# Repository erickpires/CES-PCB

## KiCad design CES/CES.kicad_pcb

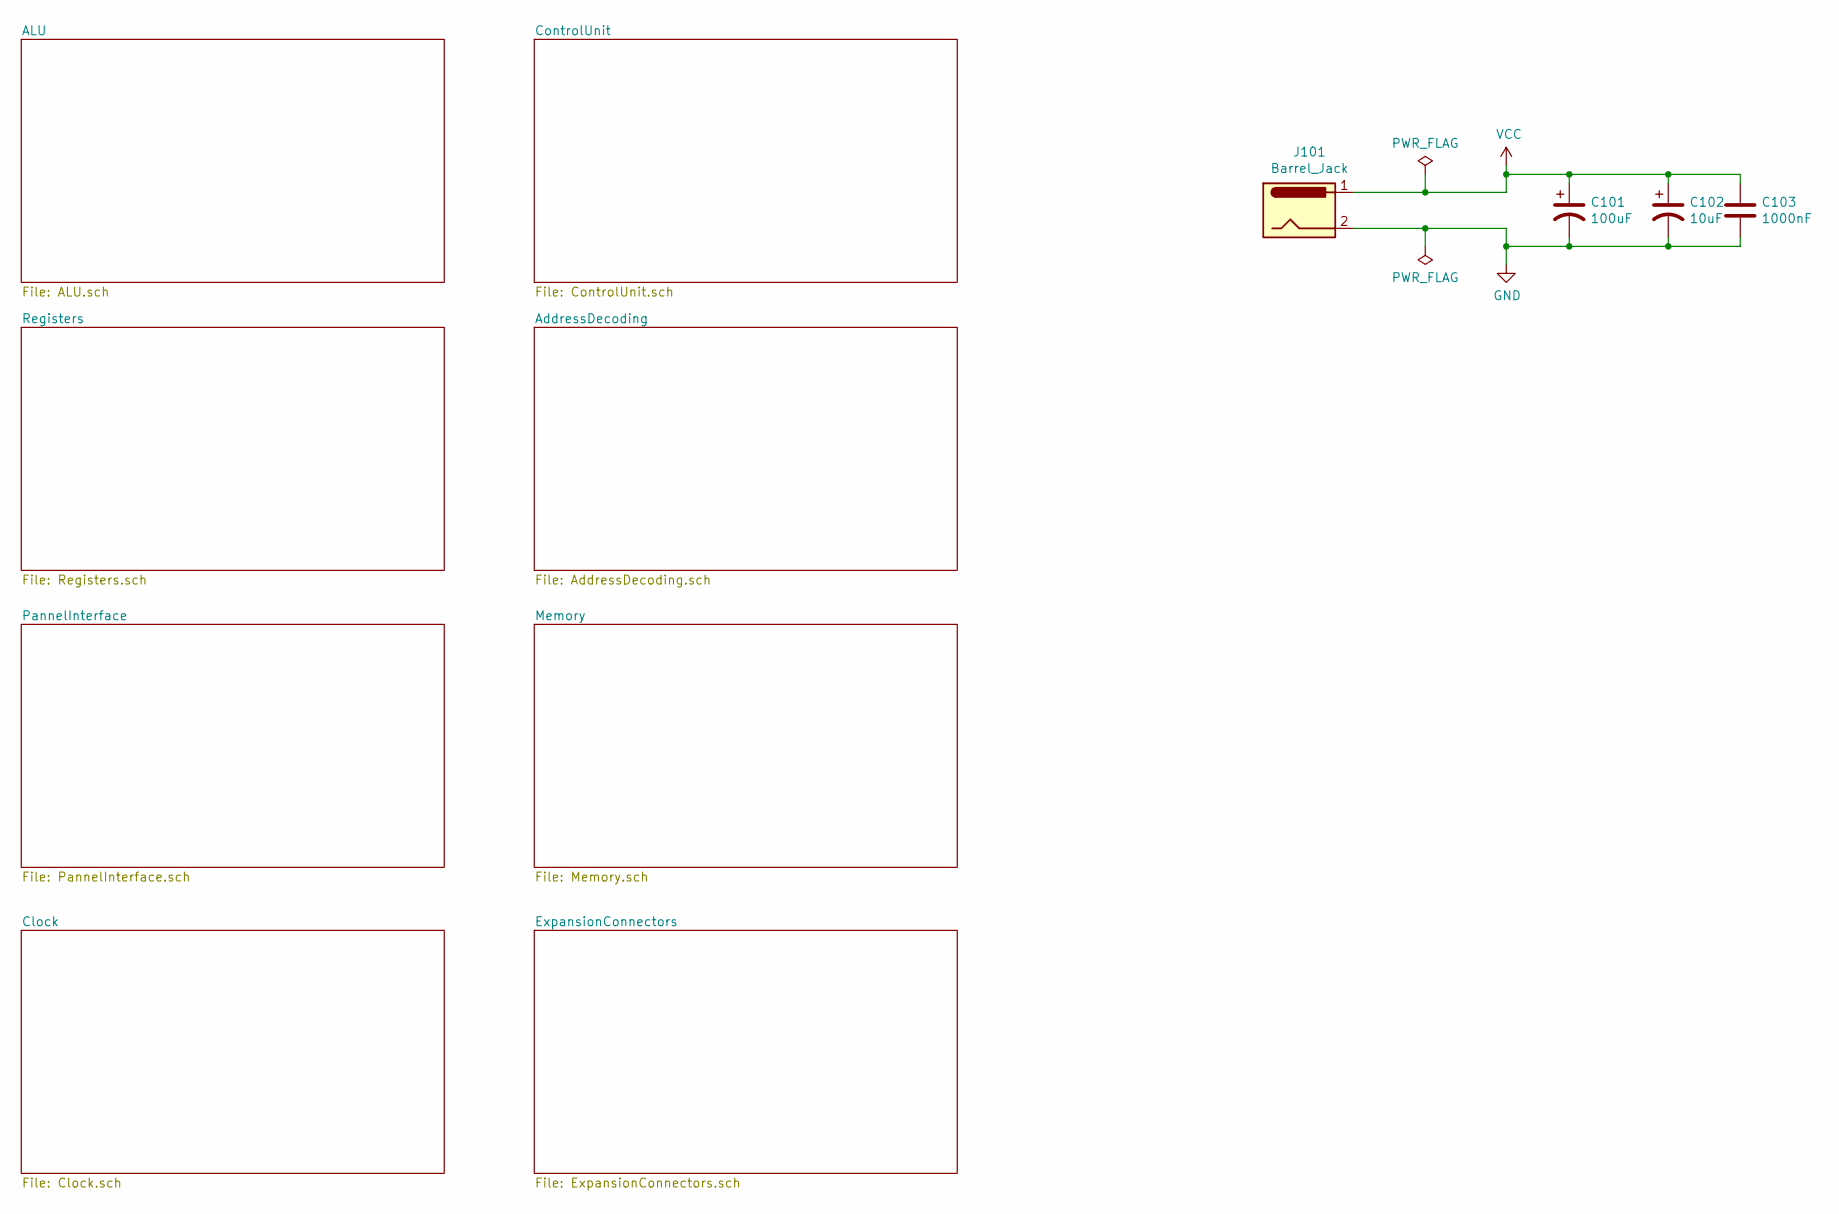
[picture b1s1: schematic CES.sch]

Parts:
C101: 100uF
C102: 10uF
C103: 1000nF
J101: Barrel_Jack

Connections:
GND: C101.2, C102.2, C103.2, J101.2; also elsewhere on the board
VCC: C101.1, C102.1, C103.1, J101.1; also elsewhere on the board

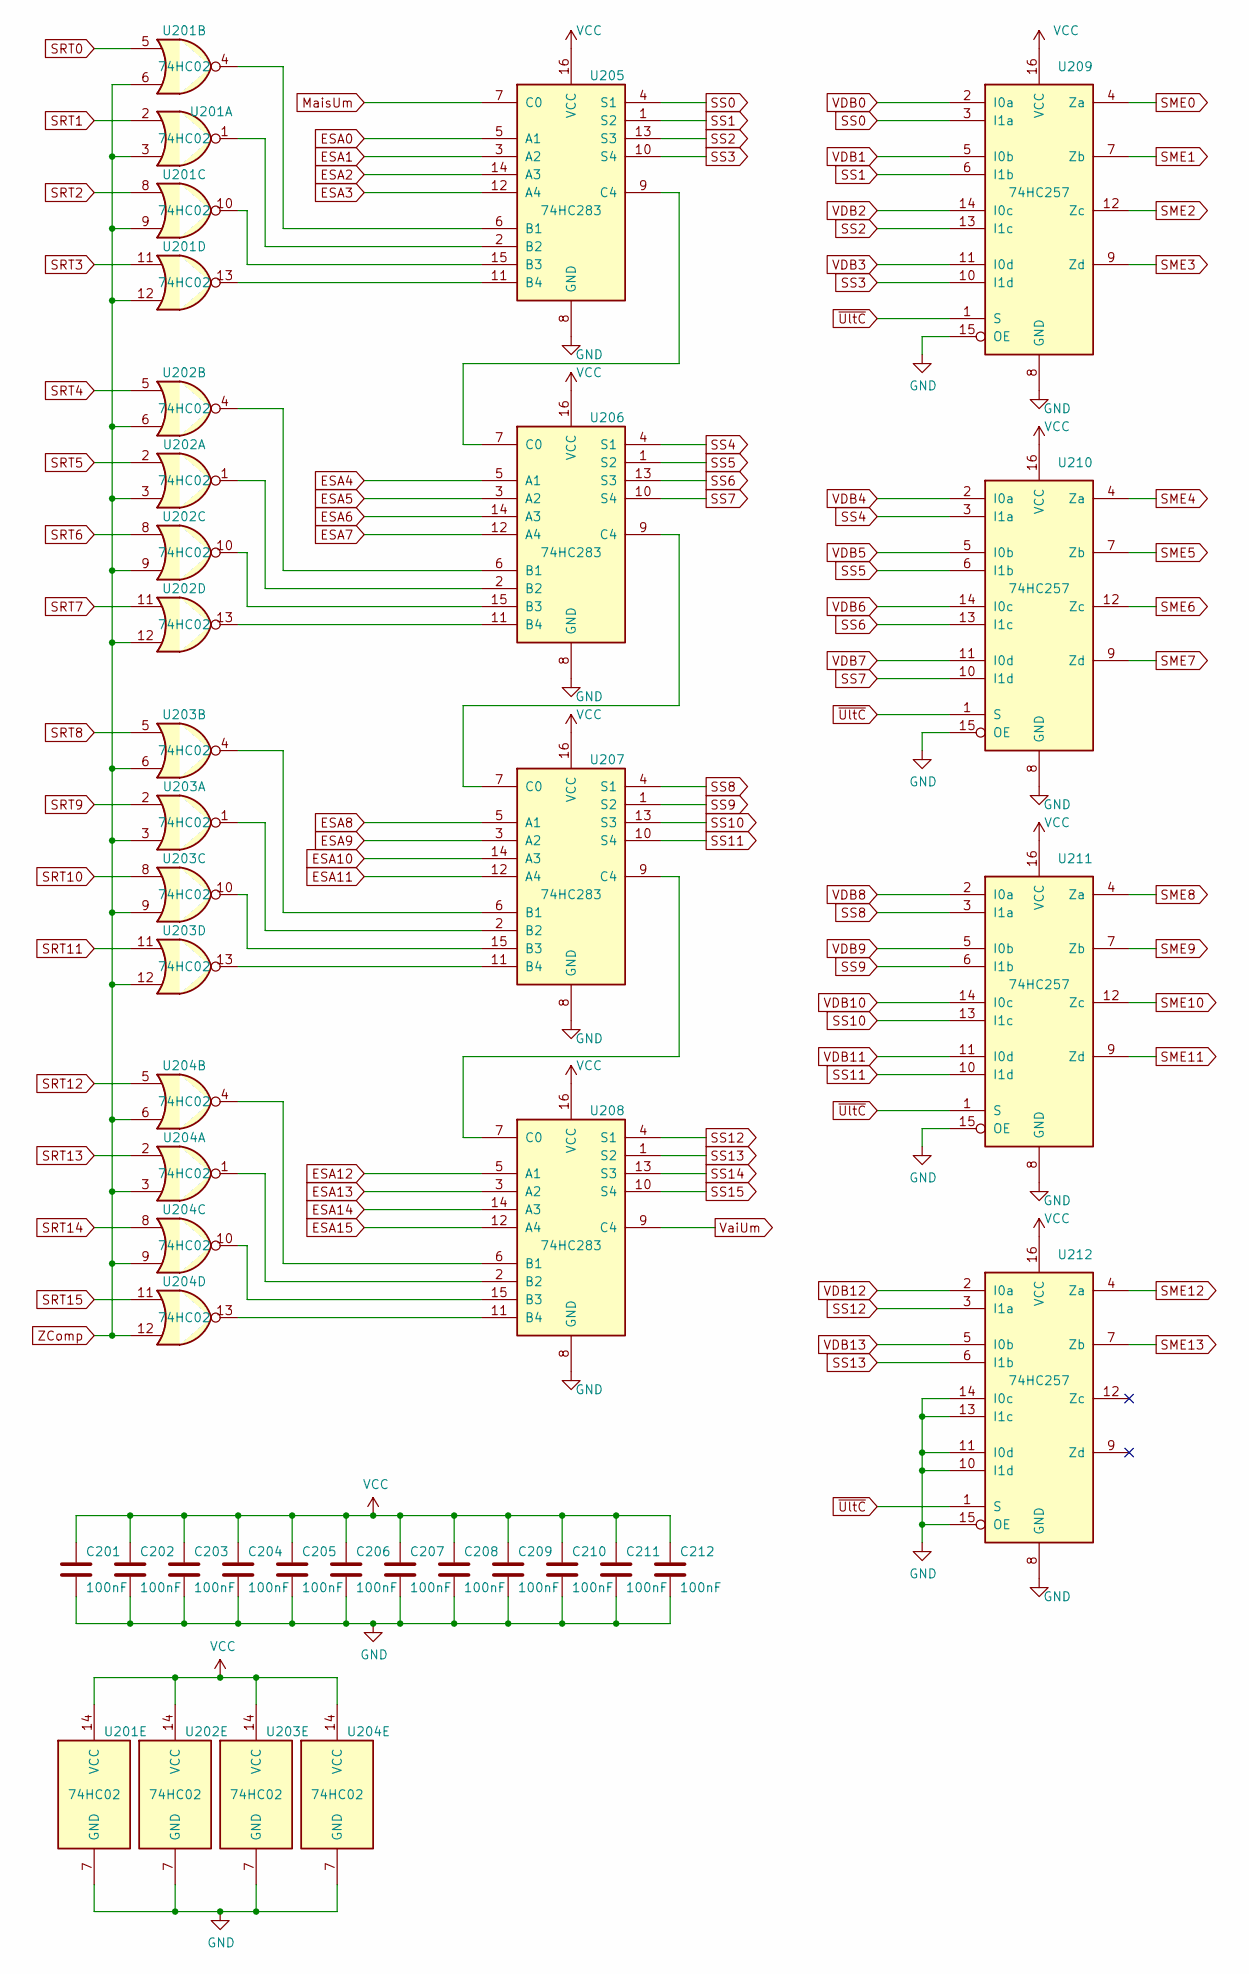
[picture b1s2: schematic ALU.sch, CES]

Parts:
C201, C202, C203, C204, C205, C206, C207, C208, C209, C210, C211, C212: 100nF; C_Disc_D4.3mm_W1.9mm_P5.00mm
U201, U202, U203, U204: 74HC02; DIP-14_W7.62mm
U205, U206, U207, U208: 74HC283; DIP-16_W7.62mm
U209, U210, U211, U212: 74HC257; DIP-16_W7.62mm

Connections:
ESA0: U205.5 (A1); also elsewhere on the board
ESA1: U205.3 (A2); also elsewhere on the board
ESA2: U205.14 (A3); also elsewhere on the board
ESA3: U205.12 (A4); also elsewhere on the board
ESA4: U206.5 (A1); also elsewhere on the board
ESA5: U206.3 (A2); also elsewhere on the board
ESA6: U206.14 (A3); also elsewhere on the board
ESA7: U206.12 (A4); also elsewhere on the board
ESA8: U207.5 (A1); also elsewhere on the board
ESA9: U207.3 (A2); also elsewhere on the board
ESA10: U207.14 (A3); also elsewhere on the board
ESA11: U207.12 (A4); also elsewhere on the board
ESA12: U208.5 (A1); also elsewhere on the board
ESA13: U208.3 (A2); also elsewhere on the board
ESA14: U208.14 (A3); also elsewhere on the board
ESA15: U208.12 (A4); also elsewhere on the board
GND: C201.2, C202.2, C203.2, C204.2, C205.2, C206.2, C207.2, C208.2, C209.2, C210.2, C211.2, C212.2, U201.7 (GND), U202.7 (GND), U203.7 (GND), U204.7 (GND), U205.8 (GND), U206.8 (GND), U207.8 (GND), U208.8 (GND), U209.8 (GND), U209.15 (OE), U210.8 (GND), U210.15 (OE), U211.8 (GND), U211.15 (OE), U212.8 (GND), U212.10 (I1d), U212.11 (I0d), U212.13 (I1c), U212.14 (I0c), U212.15 (OE); also elsewhere on the board
MaisUm: U205.7 (C0); also elsewhere on the board
unnamed: U201.1, U205.2 (B2)
unnamed: U201.4, U205.6 (B1)
unnamed: U201.10, U205.15 (B3)
unnamed: U201.13, U205.11 (B4)
unnamed: U202.1, U206.2 (B2)
unnamed: U202.4, U206.6 (B1)
unnamed: U202.10, U206.15 (B3)
unnamed: U202.13, U206.11 (B4)
unnamed: U203.1, U207.2 (B2)
unnamed: U203.4, U207.6 (B1)
unnamed: U203.10, U207.15 (B3)
unnamed: U203.13, U207.11 (B4)
unnamed: U204.1, U208.2 (B2)
unnamed: U204.4, U208.6 (B1)
unnamed: U204.10, U208.15 (B3)
unnamed: U204.13, U208.11 (B4)
unnamed: U205.9 (C4), U206.7 (C0)
unnamed: U206.9 (C4), U207.7 (C0)
unnamed: U207.9 (C4), U208.7 (C0)
SME0: U209.4 (Za); also elsewhere on the board
SME1: U209.7 (Zb); also elsewhere on the board
SME2: U209.12 (Zc); also elsewhere on the board
SME3: U209.9 (Zd); also elsewhere on the board
SME4: U210.4 (Za); also elsewhere on the board
SME5: U210.7 (Zb); also elsewhere on the board
SME6: U210.12 (Zc); also elsewhere on the board
SME7: U210.9 (Zd); also elsewhere on the board
SME8: U211.4 (Za); also elsewhere on the board
SME9: U211.7 (Zb); also elsewhere on the board
SME10: U211.12 (Zc); also elsewhere on the board
SME11: U211.9 (Zd); also elsewhere on the board
SME12: U212.4 (Za); also elsewhere on the board
SME13: U212.7 (Zb); also elsewhere on the board
SRT0: U201.5; also elsewhere on the board
SRT1: U201.2; also elsewhere on the board
SRT2: U201.8; also elsewhere on the board
SRT3: U201.11; also elsewhere on the board
SRT4: U202.5; also elsewhere on the board
SRT5: U202.2; also elsewhere on the board
SRT6: U202.8; also elsewhere on the board
SRT7: U202.11; also elsewhere on the board
SRT8: U203.5; also elsewhere on the board
SRT9: U203.2; also elsewhere on the board
SRT10: U203.8; also elsewhere on the board
SRT11: U203.11; also elsewhere on the board
SRT12: U204.5; also elsewhere on the board
SRT13: U204.2; also elsewhere on the board
SRT14: U204.8; also elsewhere on the board
SRT15: U204.11; also elsewhere on the board
SS0: U205.4 (S1), U209.3 (I1a); also elsewhere on the board
SS1: U205.1 (S2), U209.6 (I1b); also elsewhere on the board
SS2: U205.13 (S3), U209.13 (I1c); also elsewhere on the board
SS3: U205.10 (S4), U209.10 (I1d); also elsewhere on the board
SS4: U206.4 (S1), U210.3 (I1a); also elsewhere on the board
SS5: U206.1 (S2), U210.6 (I1b); also elsewhere on the board
SS6: U206.13 (S3), U210.13 (I1c); also elsewhere on the board
SS7: U206.10 (S4), U210.10 (I1d); also elsewhere on the board
SS8: U207.4 (S1), U211.3 (I1a); also elsewhere on the board
SS9: U207.1 (S2), U211.6 (I1b); also elsewhere on the board
SS10: U207.13 (S3), U211.13 (I1c); also elsewhere on the board
SS11: U207.10 (S4), U211.10 (I1d); also elsewhere on the board
SS12: U208.4 (S1), U212.3 (I1a); also elsewhere on the board
SS13: U208.1 (S2), U212.6 (I1b); also elsewhere on the board
SS14: U208.13 (S3); also elsewhere on the board
SS15: U208.10 (S4); also elsewhere on the board
VCC: C201.1, C202.1, C203.1, C204.1, C205.1, C206.1, C207.1, C208.1, C209.1, C210.1, C211.1, C212.1, U201.14 (VCC), U202.14 (VCC), U203.14 (VCC), U204.14 (VCC), U205.16 (VCC), U206.16 (VCC), U207.16 (VCC), U208.16 (VCC), U209.16 (VCC), U210.16 (VCC), U211.16 (VCC), U212.16 (VCC); also elsewhere on the board
VDB0: U209.2 (I0a); also elsewhere on the board
VDB1: U209.5 (I0b); also elsewhere on the board
VDB2: U209.14 (I0c); also elsewhere on the board
VDB3: U209.11 (I0d); also elsewhere on the board
VDB4: U210.2 (I0a); also elsewhere on the board
VDB5: U210.5 (I0b); also elsewhere on the board
VDB6: U210.14 (I0c); also elsewhere on the board
VDB7: U210.11 (I0d); also elsewhere on the board
VDB8: U211.2 (I0a); also elsewhere on the board
VDB9: U211.5 (I0b); also elsewhere on the board
VDB10: U211.14 (I0c); also elsewhere on the board
VDB11: U211.11 (I0d); also elsewhere on the board
VDB12: U212.2 (I0a); also elsewhere on the board
VDB13: U212.5 (I0b); also elsewhere on the board
VaiUm: U208.9 (C4); also elsewhere on the board
ZComp: U201.3, U201.6, U201.9, U201.12, U202.3, U202.6, U202.9, U202.12, U203.3, U203.6, U203.9, U203.12, U204.3, U204.6, U204.9, U204.12; also elsewhere on the board
~UltC: U209.1 (S), U210.1 (S), U211.1 (S), U212.1 (S); also elsewhere on the board

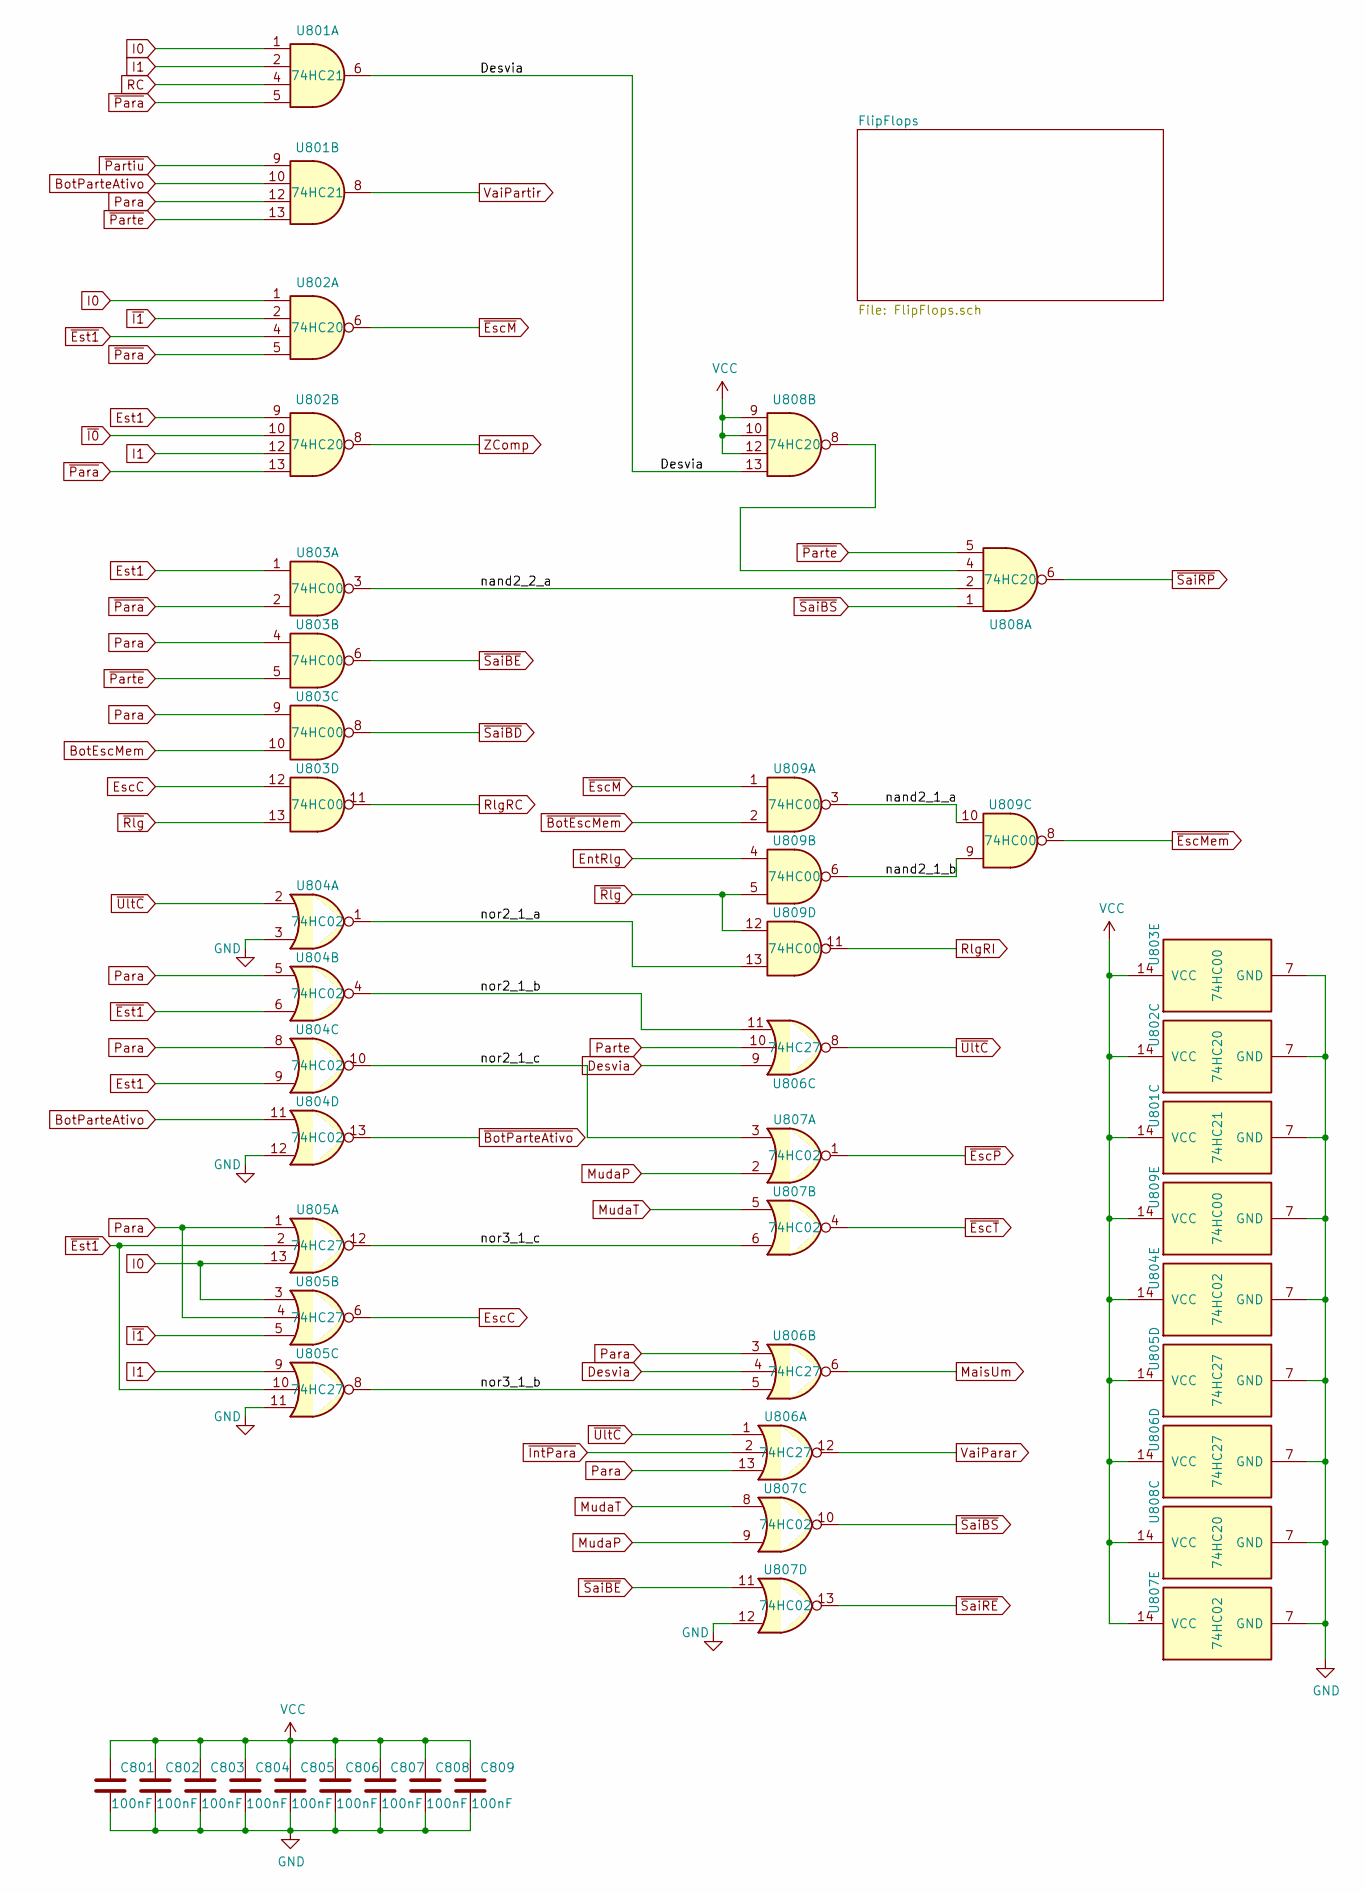
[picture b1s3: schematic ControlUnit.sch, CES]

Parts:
C801, C802, C803, C804, C805, C806, C807, C808, C809: 100nF; C_Disc_D4.3mm_W1.9mm_P5.00mm
U801: 74HC21; DIP-14_W7.62mm
U802, U808: 74HC20; DIP-14_W7.62mm
U803, U809: 74HC00; DIP-14_W7.62mm
U804, U807: 74HC02; DIP-14_W7.62mm
U805, U806: 74HC27; DIP-14_W7.62mm

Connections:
/ControlUnit/nand2_1_a: U809.3, U809.10
/ControlUnit/nand2_1_b: U809.6, U809.9
/ControlUnit/nand2_2_a: U803.3, U808.2
/ControlUnit/nor2_1_a: U804.1, U809.13
/ControlUnit/nor2_1_b: U804.4, U806.11
/ControlUnit/nor2_1_c: U804.10, U807.3
/ControlUnit/nor3_1_b: U805.8, U806.5
/ControlUnit/nor3_1_c: U805.12, U807.6
BotEscMem: U803.10; also elsewhere on the board
BotParteAtivo: U801.10, U804.11; also elsewhere on the board
Desvia: U801.6, U806.4, U806.9, U808.13
EntRlg: U809.4; also elsewhere on the board
EscC: U803.12, U805.6
Est1: U802.9, U803.1, U804.9; also elsewhere on the board
GND: C801.2, C802.2, C803.2, C804.2, C805.2, C806.2, C807.2, C808.2, C809.2, U801.7 (GND), U802.7 (GND), U803.7 (GND), U804.3, U804.7 (GND), U804.12, U805.7 (GND), U805.11, U806.7 (GND), U807.7 (GND), U807.12, U808.7 (GND), U809.7 (GND); also elsewhere on the board
I0: U801.1, U802.1, U805.3, U805.13; also elsewhere on the board
I1: U801.2, U802.12, U805.9; also elsewhere on the board
MaisUm: U806.6; also elsewhere on the board
MudaP: U807.2, U807.9; also elsewhere on the board
MudaT: U807.5, U807.8; also elsewhere on the board
unnamed: U808.4, U808.8
Para: U801.12, U803.4, U803.9, U804.5, U804.8, U805.1, U805.4, U806.3, U806.13; also elsewhere on the board
Parte: U806.10; also elsewhere on the board
RC: U801.4; also elsewhere on the board
RlgRC: U803.11; also elsewhere on the board
RlgRI: U809.11; also elsewhere on the board
VCC: C801.1, C802.1, C803.1, C804.1, C805.1, C806.1, C807.1, C808.1, C809.1, U801.14 (VCC), U802.14 (VCC), U803.14 (VCC), U804.14 (VCC), U805.14 (VCC), U806.14 (VCC), U807.14 (VCC), U808.9, U808.10, U808.12, U808.14 (VCC), U809.14 (VCC); also elsewhere on the board
VaiParar: U806.12; also elsewhere on the board
VaiPartir: U801.8; also elsewhere on the board
ZComp: U802.8; also elsewhere on the board
~BotEscMem: U809.2; also elsewhere on the board
~BotParteAtivo: U804.13; also elsewhere on the board
~EscM: U802.6, U809.1; also elsewhere on the board
~EscMem: U809.8; also elsewhere on the board
~EscP: U807.1; also elsewhere on the board
~EscT: U807.4; also elsewhere on the board
~Est1: U802.4, U804.6, U805.2, U805.10; also elsewhere on the board
~I0: U802.10; also elsewhere on the board
~I1: U802.2, U805.5; also elsewhere on the board
~IntPara: U806.2; also elsewhere on the board
~Para: U801.5, U802.5, U802.13, U803.2; also elsewhere on the board
~Parte: U801.13, U803.5, U808.5; also elsewhere on the board
~Partiu: U801.9; also elsewhere on the board
~Rlg: U803.13, U809.5, U809.12; also elsewhere on the board
~SaiBD: U803.8; also elsewhere on the board
~SaiBE: U803.6, U807.11; also elsewhere on the board
~SaiBS: U807.10, U808.1; also elsewhere on the board
~SaiRE: U807.13; also elsewhere on the board
~SaiRP: U808.6; also elsewhere on the board
~UltC: U804.2, U806.1, U806.8; also elsewhere on the board

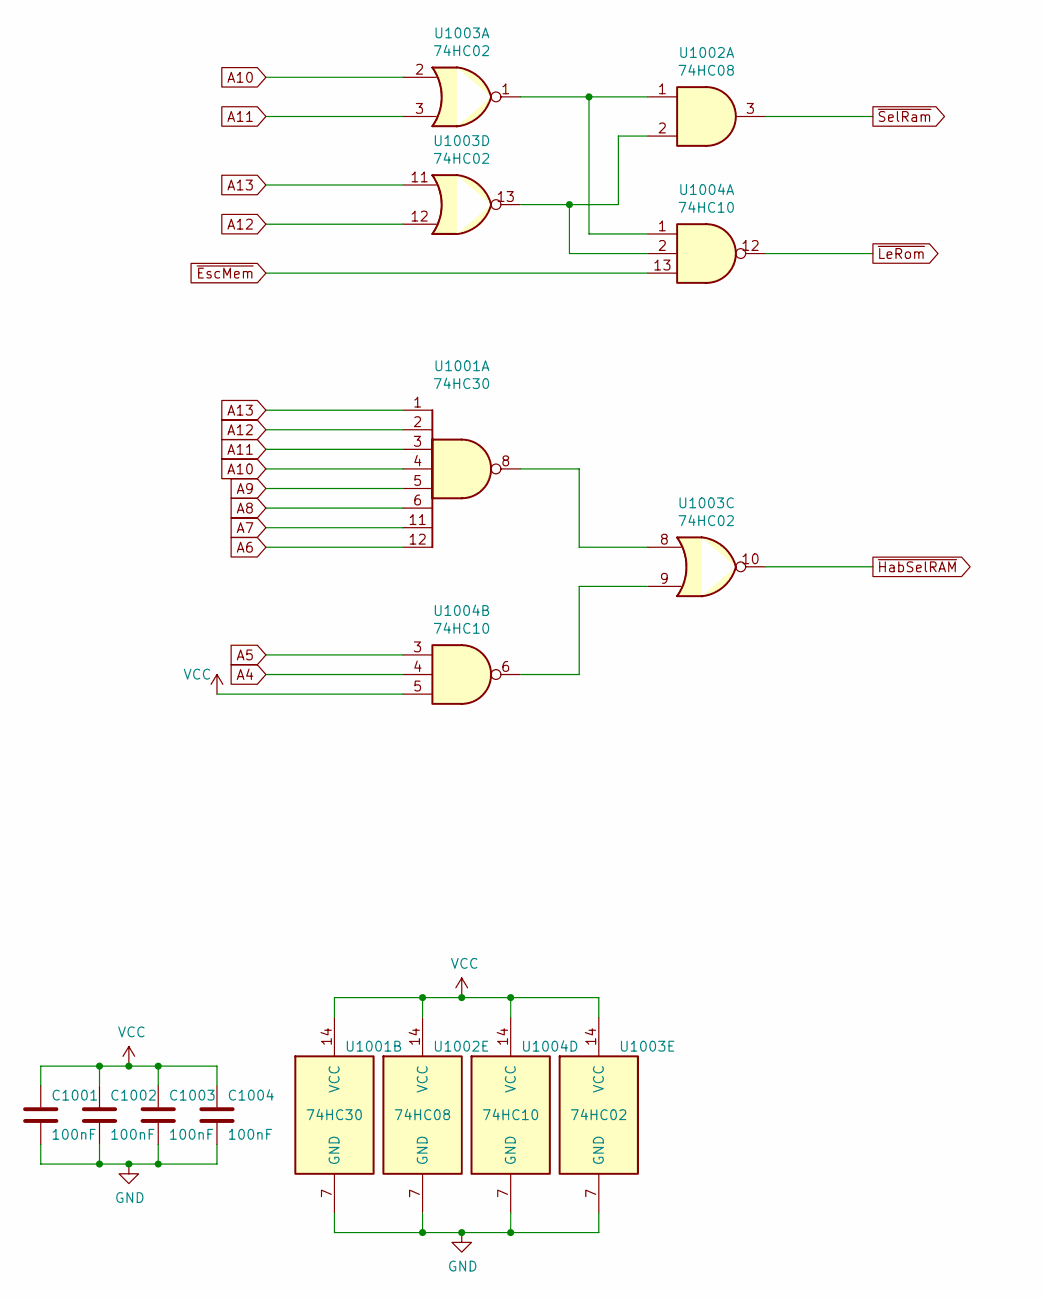
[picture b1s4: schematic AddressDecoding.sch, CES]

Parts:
C1001, C1002, C1003, C1004: 100nF; C_Disc_D4.3mm_W1.9mm_P5.00mm
U1001: 74HC30; DIP-14_W7.62mm
U1002: 74HC08; DIP-14_W7.62mm
U1003: 74HC02; DIP-14_W7.62mm
U1004: 74HC10; DIP-14_W7.62mm

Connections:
A4: U1004.4; also elsewhere on the board
A5: U1004.3; also elsewhere on the board
A6: U1001.12; also elsewhere on the board
A7: U1001.11; also elsewhere on the board
A8: U1001.6; also elsewhere on the board
A9: U1001.5; also elsewhere on the board
A10: U1001.4, U1003.2; also elsewhere on the board
A11: U1001.3, U1003.3; also elsewhere on the board
A12: U1001.2, U1003.12; also elsewhere on the board
A13: U1001.1, U1003.11; also elsewhere on the board
GND: C1001.2, C1002.2, C1003.2, C1004.2, U1001.7 (GND), U1002.4, U1002.5, U1002.7 (GND), U1002.9, U1002.10, U1002.12, U1002.13, U1003.5, U1003.6, U1003.7 (GND), U1004.7 (GND), U1004.9, U1004.10, U1004.11; also elsewhere on the board
unnamed: U1001.8, U1003.8
unnamed: U1002.1, U1003.1, U1004.1
unnamed: U1002.2, U1003.13, U1004.2
unnamed: U1003.9, U1004.6
VCC: C1001.1, C1002.1, C1003.1, C1004.1, U1001.14 (VCC), U1002.14 (VCC), U1003.14 (VCC), U1004.5, U1004.14 (VCC); also elsewhere on the board
~EscMem: U1004.13; also elsewhere on the board
~HabSelRAM: U1003.10; also elsewhere on the board
~LeRom: U1004.12; also elsewhere on the board
~SelRam: U1002.3; also elsewhere on the board

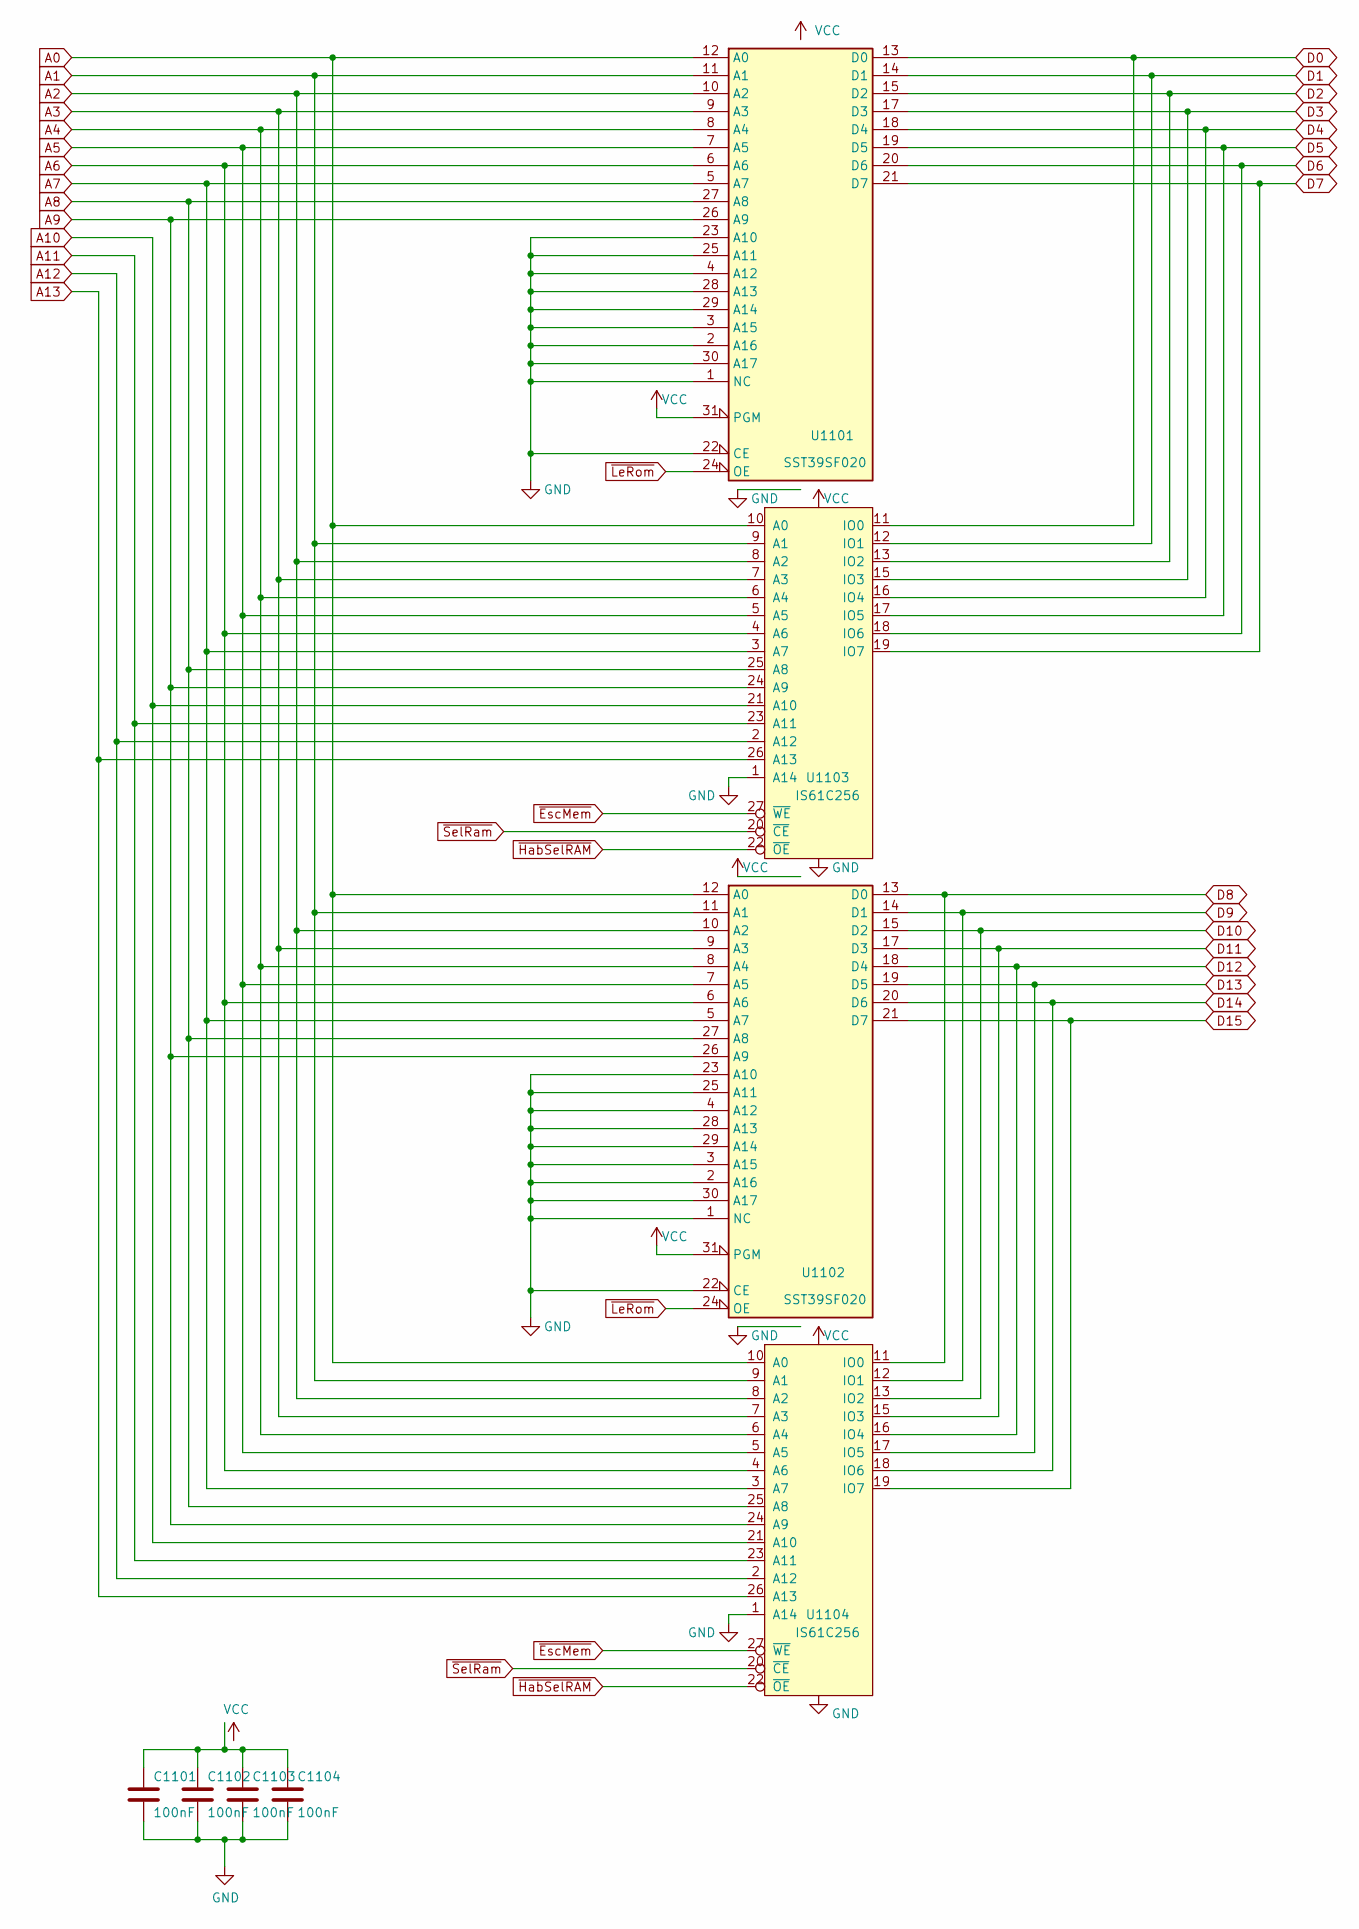
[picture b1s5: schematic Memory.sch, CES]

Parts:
C1101, C1102, C1103, C1104: 100nF; C_Disc_D4.3mm_W1.9mm_P5.00mm
U1101, U1102: SST39SF020; DIP-32_W15.24mm_Socket
U1103, U1104: IS61C256; DIP-28_W7.62mm

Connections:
A0: U1101.12 (A0), U1102.12 (A0), U1103.10 (A0), U1104.10 (A0); also elsewhere on the board
A1: U1101.11 (A1), U1102.11 (A1), U1103.9 (A1), U1104.9 (A1); also elsewhere on the board
A2: U1101.10 (A2), U1102.10 (A2), U1103.8 (A2), U1104.8 (A2); also elsewhere on the board
A3: U1101.9 (A3), U1102.9 (A3), U1103.7 (A3), U1104.7 (A3); also elsewhere on the board
A4: U1101.8 (A4), U1102.8 (A4), U1103.6 (A4), U1104.6 (A4); also elsewhere on the board
A5: U1101.7 (A5), U1102.7 (A5), U1103.5 (A5), U1104.5 (A5); also elsewhere on the board
A6: U1101.6 (A6), U1102.6 (A6), U1103.4 (A6), U1104.4 (A6); also elsewhere on the board
A7: U1101.5 (A7), U1102.5 (A7), U1103.3 (A7), U1104.3 (A7); also elsewhere on the board
A8: U1101.27 (A8), U1102.27 (A8), U1103.25 (A8), U1104.25 (A8); also elsewhere on the board
A9: U1101.26 (A9), U1102.26 (A9), U1103.24 (A9), U1104.24 (A9); also elsewhere on the board
A10: U1103.21 (A10), U1104.21 (A10); also elsewhere on the board
A11: U1103.23 (A11), U1104.23 (A11); also elsewhere on the board
A12: U1103.2 (A12), U1104.2 (A12); also elsewhere on the board
A13: U1103.26 (A13), U1104.26 (A13); also elsewhere on the board
D0: U1101.13 (D0), U1103.11 (IO0); also elsewhere on the board
D1: U1101.14 (D1), U1103.12 (IO1); also elsewhere on the board
D2: U1101.15 (D2), U1103.13 (IO2); also elsewhere on the board
D3: U1101.17 (D3), U1103.15 (IO3); also elsewhere on the board
D4: U1101.18 (D4), U1103.16 (IO4); also elsewhere on the board
D5: U1101.19 (D5), U1103.17 (IO5); also elsewhere on the board
D6: U1101.20 (D6), U1103.18 (IO6); also elsewhere on the board
D7: U1101.21 (D7), U1103.19 (IO7); also elsewhere on the board
D8: U1102.13 (D0), U1104.11 (IO0); also elsewhere on the board
D9: U1102.14 (D1), U1104.12 (IO1); also elsewhere on the board
D10: U1102.15 (D2), U1104.13 (IO2); also elsewhere on the board
D11: U1102.17 (D3), U1104.15 (IO3); also elsewhere on the board
D12: U1102.18 (D4), U1104.16 (IO4); also elsewhere on the board
D13: U1102.19 (D5), U1104.17 (IO5); also elsewhere on the board
D14: U1102.20 (D6), U1104.18 (IO6); also elsewhere on the board
D15: U1102.21 (D7), U1104.19 (IO7); also elsewhere on the board
GND: C1101.2, C1102.2, C1103.2, C1104.2, U1101.1 (NC), U1101.2 (A16), U1101.3 (A15), U1101.4 (A12), U1101.16 (GND), U1101.22 (CE), U1101.23 (A10), U1101.25 (A11), U1101.28 (A13), U1101.29 (A14), U1101.30 (A17), U1102.1 (NC), U1102.2 (A16), U1102.3 (A15), U1102.4 (A12), U1102.16 (GND), U1102.22 (CE), U1102.23 (A10), U1102.25 (A11), U1102.28 (A13), U1102.29 (A14), U1102.30 (A17), U1103.1 (A14), U1103.14 (GND), U1104.1 (A14), U1104.14 (GND); also elsewhere on the board
unnamed: C1101.1, C1102.1, C1103.1, C1104.1
VCC: U1101.31 (PGM), U1101.32 (VCC), U1102.31 (PGM), U1102.32 (VCC), U1103.28 (VCC), U1104.28 (VCC); also elsewhere on the board
~EscMem: U1103.27 (~WE), U1104.27 (~WE); also elsewhere on the board
~HabSelRAM: U1103.22 (~OE), U1104.22 (~OE); also elsewhere on the board
~LeRom: U1101.24 (OE), U1102.24 (OE); also elsewhere on the board
~SelRam: U1103.20 (~CE), U1104.20 (~CE); also elsewhere on the board

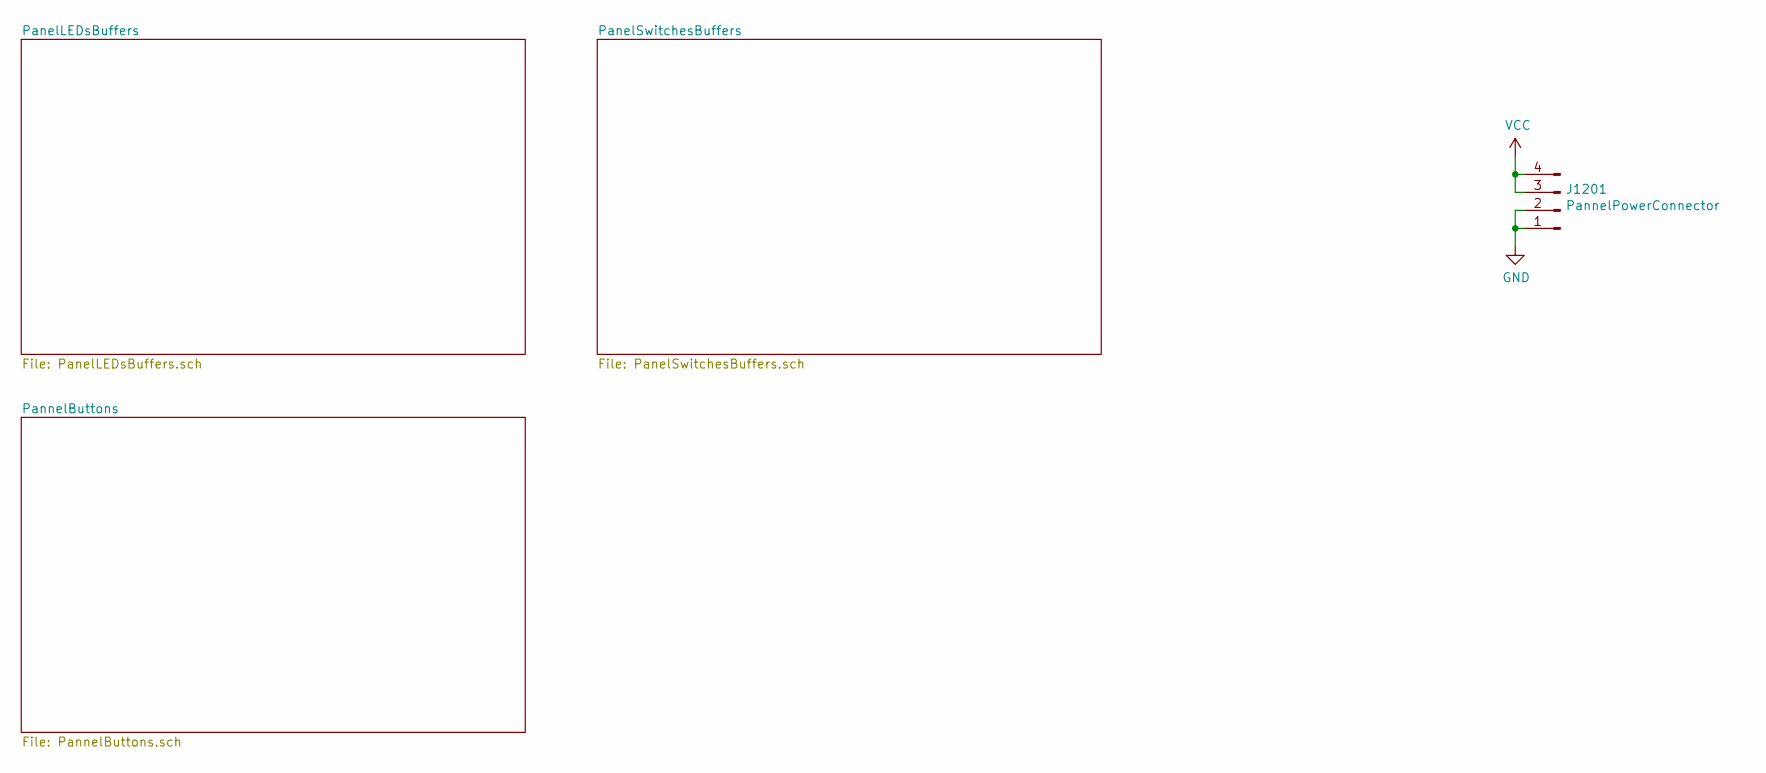
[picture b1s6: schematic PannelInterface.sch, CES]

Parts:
J1201: PannelPowerConnector

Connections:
GND: J1201.1, J1201.2; also elsewhere on the board
VCC: J1201.3, J1201.4; also elsewhere on the board

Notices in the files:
CES/ALU.sch:
Copyright 2021 Erick Pires
